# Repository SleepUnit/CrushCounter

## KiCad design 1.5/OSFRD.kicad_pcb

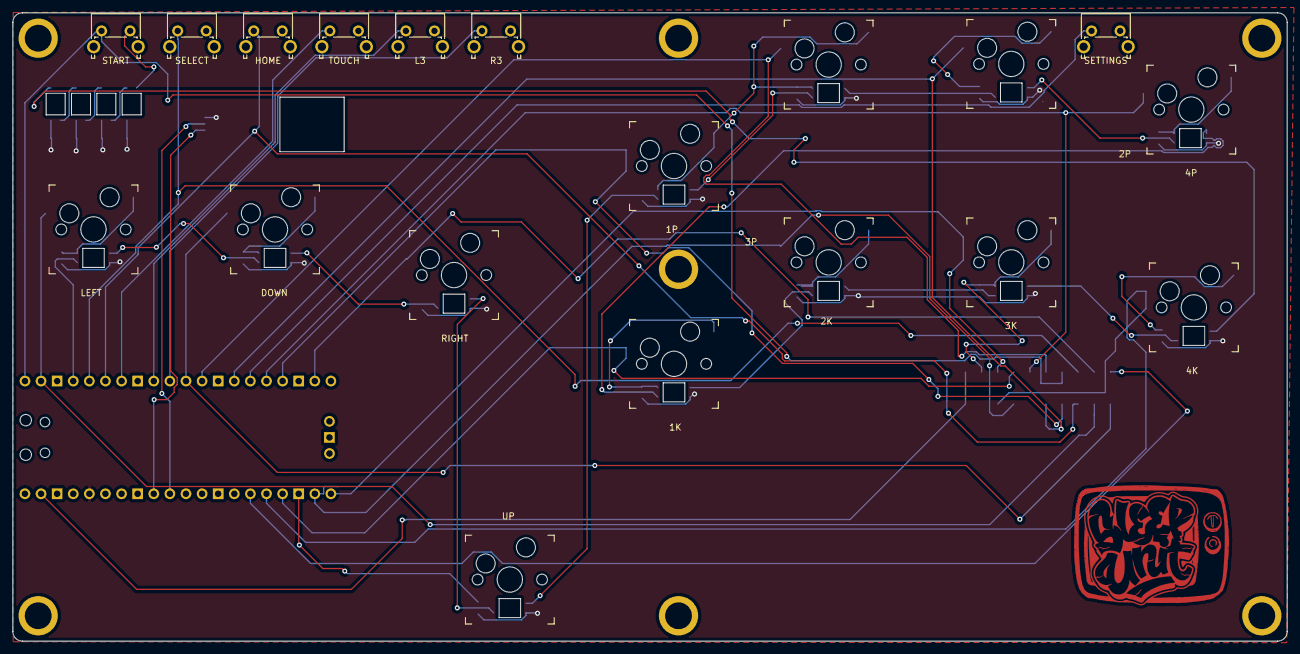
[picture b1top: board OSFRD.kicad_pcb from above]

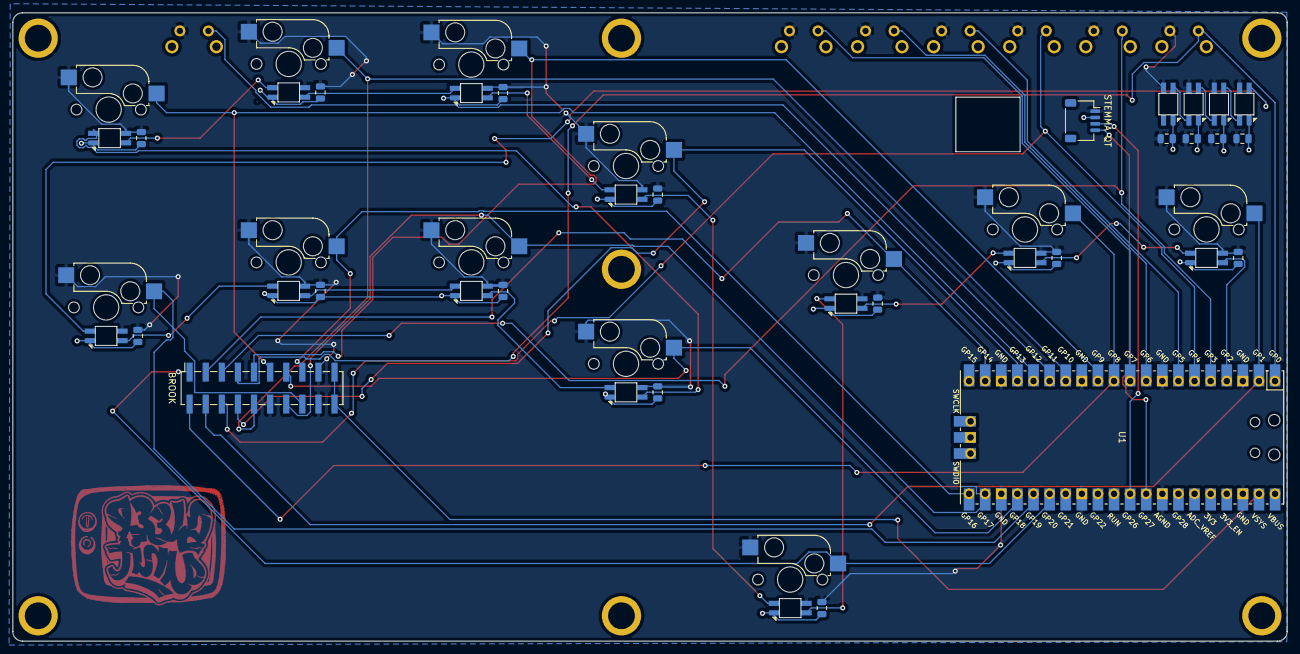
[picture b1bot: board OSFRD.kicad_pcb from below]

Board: 2 copper layers, 201.0 x 99.1 mm, 54 parts (35 on the bottom side), 40 nets.

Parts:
BROOK: 20 Pin; PinSocket_2x10_P2.54mm_Vertical_SMD
HOME: SW_PUSH; SW_Tactile_SPST_Angled_PTS645Vx83-2LFS
L3: SW_PUSH; SW_Tactile_SPST_Angled_PTS645Vx83-2LFS
R3: SW_PUSH; SW_Tactile_SPST_Angled_PTS645Vx83-2LFS
SELECT: SW_PUSH; SW_Tactile_SPST_Angled_PTS645Vx83-2LFS
SETTINGS: SW_PUSH; SW_Tactile_SPST_Angled_PTS645Vx83-2LFS
START: SW_PUSH; SW_Tactile_SPST_Angled_PTS645Vx83-2LFS
STEMMA QT: STEMMA QT; JST_SH_SM04B-SRSS-TB_1x04-1MP_P1.00mm_Horizontal
SW-P1, SW-P2, SW-P3, SW-P4, SW-P5, SW-P6, SW-P7, SW-P8, SW-P9, SW-P10, SW-P11, SW-P12: KEYSW; Kailh_socket_MX
TOUCH: SW_PUSH; SW_Tactile_SPST_Angled_PTS645Vx83-2LFS
U1: Pico; RPi_Pico_SMD_TH
U-CAP1, U-CAP2, U-CAP3, U-CAP4, U-CAP5, U-CAP6, U-CAP7, U-CAP8, U-CAP9, U-CAP10, U-CAP11, U-CAP12, U-CAP13, U-CAP14, U-CAP15, U-CAP16: 0.1uF; C_0805_2012Metric
U-RGB1, U-RGB2, U-RGB3, U-RGB4, U-RGB5, U-RGB6, U-RGB7, U-RGB8, U-RGB9, U-RGB10, U-RGB11, U-RGB12, U-RGB13, U-RGB14, U-RGB15, U-RGB16: Reverse Mounted NeoPixel; SK6812-MINI-E

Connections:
+3V3: STEMMA QT.2, U1.36, U-CAP1.2, U-CAP2.2, U-CAP3.2, U-CAP4.2, U-CAP5.2, U-CAP6.2, U-CAP7.2, U-CAP8.2, U-CAP9.2, U-CAP10.2, U-CAP11.2, U-CAP12.2, U-CAP13.2, U-CAP14.2, U-CAP15.2, U-CAP16.2, U-RGB1.3, U-RGB2.3, U-RGB3.3, U-RGB4.3, U-RGB5.3, U-RGB6.3, U-RGB7.3, U-RGB8.3, U-RGB9.3, U-RGB10.3, U-RGB11.3, U-RGB12.3, U-RGB13.3, U-RGB14.3, U-RGB15.3, U-RGB16.3
+5V: BROOK.19, BROOK.20, U1.39
/Buttons/sheet61498D2A/DataIn: U-RGB5.4, U-RGB6.2
/Buttons/sheet61498D2B/DataIn: U-RGB6.4, U-RGB7.2
/Buttons/sheet61498D2C/DataIn: U-RGB7.4, U-RGB8.2
/Buttons/sheet61498D2D/DataIn: U-RGB8.4, U-RGB9.2
/Buttons/sheet61498D2E/DataIn: U-RGB9.4, U-RGB10.2
/Buttons/sheet61498D2F/DataIn: U-RGB10.4, U-RGB11.2
/Buttons/sheet61498D25/DataIn: U-RGB1.2, U-RGB4.4
/Buttons/sheet61498D26/DataIn: U-RGB2.2, U-RGB3.4
/Buttons/sheet61498D28/DataIn: U-RGB2.4, U-RGB4.2
/Buttons/sheet61498D29/DataIn: U-RGB1.4, U-RGB5.2
/Buttons/sheet61498D30/DataIn: U-RGB11.4, U-RGB12.2
/GPIO0: BROOK.7, START.1, U1.1
/GPIO1: BROOK.4, SW-P3.2, U1.2
/GPIO2: U1.4, U-RGB3.2
/GPIO3: BROOK.5, SELECT.1, U1.5
/GPIO4: BROOK.6, HOME.1, U1.6
/GPIO5: TOUCH.1, U1.7
/GPIO6: L3.1, U1.9
/GPIO7: R3.1, U1.10
/GPIO8: BROOK.2, SW-P2.2, U1.11
/GPIO9: BROOK.9, SW-P6.2, U1.12
/GPIO10: BROOK.10, SW-P7.2, U1.14
/GPIO11: SETTINGS.1, U1.15
/GPIO12: BROOK.11, SW-P8.2, U1.16
/GPIO13: BROOK.8, SW-P5.2, U1.17
/GPIO14: BROOK.3, SW-P4.2, U1.19
/GPIO16: BROOK.15, SW-P11.2, U1.21
/GPIO17: BROOK.14, SW-P10.2, U1.22
/GPIO18: BROOK.13, SW-P9.2, U1.24
/GPIO19: BROOK.16, SW-P12.2, U1.25
/GPIO20: BROOK.1, SW-P1.2, U1.26
/GPIO26_I2C1_SDA: STEMMA QT.3, U1.31
/GPIO27_I2C1_SCL: STEMMA QT.4, U1.32
/PlayerPixels: U-RGB12.4, U-RGB13.2
GND: BROOK.12, BROOK.17, BROOK.18, HOME.2, L3.2, R3.2, SELECT.2, SETTINGS.2, START.2, STEMMA QT.1, SW-P1.1, SW-P2.1, SW-P3.1, SW-P4.1, SW-P5.1, SW-P6.1, SW-P7.1, SW-P8.1, SW-P9.1, SW-P10.1, SW-P11.1, SW-P12.1, TOUCH.2, U1.3, U1.8, U1.13, U1.18, U1.23, U1.28, U1.33, U1.38, U-CAP1.1, U-CAP2.1, U-CAP3.1, U-CAP4.1, U-CAP5.1, U-CAP6.1, U-CAP7.1, U-CAP8.1, U-CAP9.1, U-CAP10.1, U-CAP11.1, U-CAP12.1, U-CAP13.1, U-CAP14.1, U-CAP15.1, U-CAP16.1, U-RGB1.1, U-RGB2.1, U-RGB3.1, U-RGB4.1, U-RGB5.1, U-RGB6.1, U-RGB7.1, U-RGB8.1, U-RGB9.1, U-RGB10.1, U-RGB11.1, U-RGB12.1, U-RGB13.1, U-RGB14.1, U-RGB15.1, U-RGB16.1
unnamed: U-RGB13.4, U-RGB14.2
unnamed: U-RGB14.4, U-RGB15.2
unnamed: U-RGB15.4, U-RGB16.2

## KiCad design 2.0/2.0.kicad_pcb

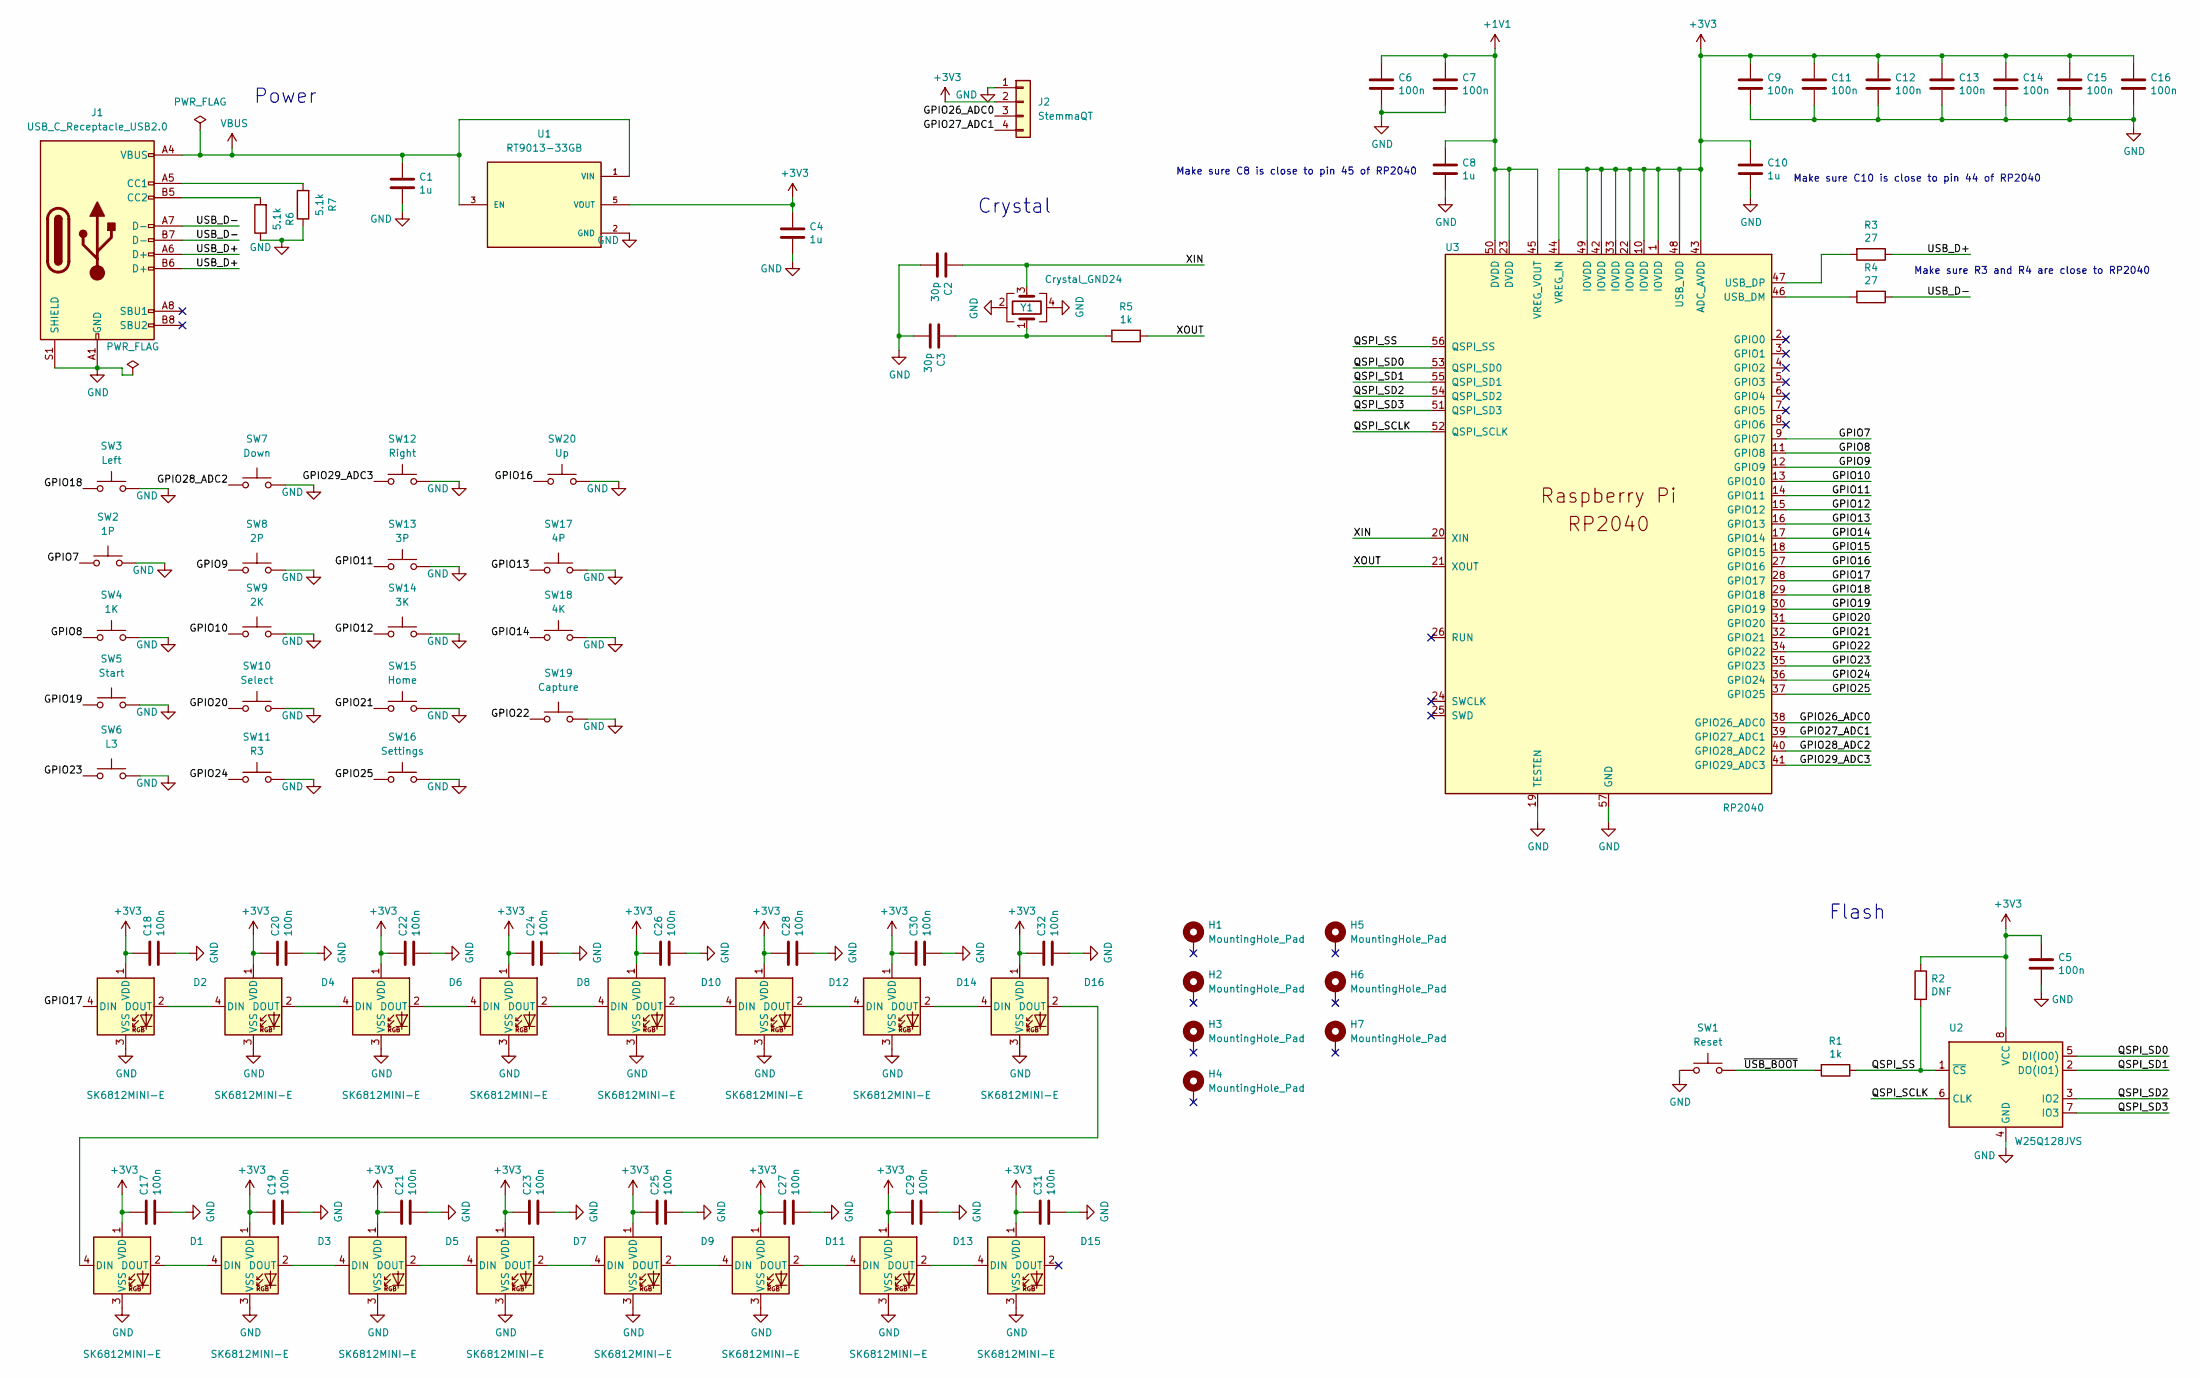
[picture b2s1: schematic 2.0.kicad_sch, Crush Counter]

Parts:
C1, C4, C8, C10: 1u; C_0402_1005Metric; PartNumber CL05A105KA5NQNC; LCSC Part C52923
C2, C3: 30p; C_0402_1005Metric; PartNumber 0402CG300J500NT; LCSC Part C1570
C5, C6, C7, C9, C11, C12, C13, C14, C15, C16, C17, C18, C19, C20, C21, C22, C23, C24, C25, C26, C27, C28, C29, C30, C31, C32: 100n; C_0402_1005Metric; PartNumber CL05B104KO5NNNC; LCSC Part C1525
D1, D2, D3, D4, D5, D6, D7, D8, D9, D10, D11, D12, D13, D14, D15, D16: SK6812MINI-E; MX_SK6812MINI-E; PartNumber SK6812MINI-E; LCSC Part DNF
H1, H2, H3, H4, H5, H6, H7: MountingHole_Pad; Mounting_Wuerth_WA-SMSI-M3_H2mm_9774020360; PartNumber SMTSO3020MTJ; LCSC Part C2915633
J1: USB_C_Receptacle_USB2.0; USB_C_Receptacle_HRO_TYPE-C-31-M-12; PartNumber HRO_TYPE-C-31-M-12; LCSC Part C165948
J2: StemmaQT; JST_SH_SM04B-SRSS-TB_1x04-1MP_P1.00mm_Horizontal; PartNumber SM04B-SRSS-TBLFSN; LCSC Part DNF
R1, R5: 1k; C_0402_1005Metric; PartNumber 0402WGF1001TCE; LCSC Part C11702
R2: DNF; C_0402_1005Metric; PartNumber DNF; LCSC Part DNF
R3, R4: 27; C_0603_1608Metric; PartNumber 0603WAF270JT5E; LCSC Part C25190
R6, R7: 5.1k; C_0402_1005Metric; PartNumber 0402WGF5101TCE; LCSC Part C25905
SW1: Reset; TS-1187A-B-A-B; PartNumber TS-1187A-B-A-B; LCSC Part C318884
SW2: 1P; Kailh_socket_MX; PartNumber PG151101S11; LCSC Part DNF
SW3: Left; Kailh_socket_MX; PartNumber PG151101S11; LCSC Part DNF
SW4: 1K; Kailh_socket_MX; PartNumber PG151101S11; LCSC Part DNF
SW5: Start; EVQP7C01P; PartNumber EVQP7C01P; LCSC Part C388883
SW6: L3; EVQP7C01P; PartNumber EVQP7C01P; LCSC Part C388883
SW7: Down; Kailh_socket_MX; PartNumber PG151101S11; LCSC Part DNF
SW8: 2P; Kailh_socket_MX; PartNumber PG151101S11; LCSC Part DNF
SW9: 2K; Kailh_socket_MX; PartNumber PG151101S11; LCSC Part DNF
SW10: Select; EVQP7C01P; PartNumber EVQP7C01P; LCSC Part C388883
SW11: R3; EVQP7C01P; PartNumber EVQP7C01P; LCSC Part C388883
SW12: Right; Kailh_socket_MX; PartNumber PG151101S11; LCSC Part DNF
SW13: 3P; Kailh_socket_MX; PartNumber PG151101S11; LCSC Part DNF
SW14: 3K; Kailh_socket_MX; PartNumber PG151101S11; LCSC Part DNF
SW15: Home; EVQP7C01P; PartNumber EVQP7C01P; LCSC Part C388883
SW16: Settings; EVQP7C01P; PartNumber EVQP7C01P; LCSC Part C388883
SW17: 4P; Kailh_socket_MX; PartNumber PG151101S11; LCSC Part DNF
SW18: 4K; Kailh_socket_MX; PartNumber PG151101S11; LCSC Part DNF
SW19: Capture; EVQP7C01P; PartNumber EVQP7C01P; LCSC Part C388883
SW20: Up; Kailh_socket_MX; PartNumber PG151101S11; LCSC Part DNF
U1: RT9013-33GB; SOT94P279X129-5N; PARTREV Aprill 2011; LCSC Part C47773
U2: W25Q128JVS; SOIC-8_5.23x5.23mm_P1.27mm; PartNumber W25Q128JVS; LCSC Part C97521
U3: RP2040; RP2040-QFN-56; PartNumber RP2040; LCSC Part C2040
Y1: Crystal_GND24; Crystal_SMD_3225-4Pin_3.2x2.5mm; PartNumber X322512MSB4SI; LCSC Part C9002

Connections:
+1V1: C6.1, C7.1, C8.1, U3.23 (DVDD), U3.45 (VREG_VOUT), U3.50 (DVDD)
+3V3: C4.1, C5.1, C9.1, C10.1, C11.1, C12.1, C13.1, C14.1, C15.1, C16.1, C17.1, C18.1, C19.1, C20.1, C21.1, C22.1, C23.1, C24.1, C25.1, C26.1, C27.1, C28.1, C29.1, C30.1, C31.1, C32.1, D1.1 (VDD), D2.1 (VDD), D3.1 (VDD), D4.1 (VDD), D5.1 (VDD), D6.1 (VDD), D7.1 (VDD), D8.1 (VDD), D9.1 (VDD), D10.1 (VDD), D11.1 (VDD), D12.1 (VDD), D13.1 (VDD), D14.1 (VDD), D15.1 (VDD), D16.1 (VDD), J2.2, R2.1, U1.5 (VOUT), U2.8 (VCC), U3.1 (IOVDD), U3.10 (IOVDD), U3.22 (IOVDD), U3.33 (IOVDD), U3.42 (IOVDD), U3.43 (ADC_AVDD), U3.44 (VREG_IN), U3.48 (USB_VDD), U3.49 (IOVDD)
/GPIO7: SW2.1, U3.9 (GPIO7)
/GPIO8: SW4.1, U3.11 (GPIO8)
/GPIO9: SW8.1, U3.12 (GPIO9)
/GPIO10: SW9.1, U3.13 (GPIO10)
/GPIO11: SW13.1, U3.14 (GPIO11)
/GPIO12: SW14.1, U3.15 (GPIO12)
/GPIO13: SW17.1, U3.16 (GPIO13)
/GPIO14: SW18.1, U3.17 (GPIO14)
/GPIO15: U3.18 (GPIO15)
/GPIO16: SW20.1, U3.27 (GPIO16)
/GPIO17: D2.4 (DIN), U3.28 (GPIO17)
/GPIO18: SW3.1, U3.29 (GPIO18)
/GPIO19: SW5.1, U3.30 (GPIO19)
/GPIO20: SW10.1, U3.31 (GPIO20)
/GPIO21: SW15.1, U3.32 (GPIO21)
/GPIO22: SW19.1, U3.34 (GPIO22)
/GPIO23: SW6.1, U3.35 (GPIO23)
/GPIO24: SW11.1, U3.36 (GPIO24)
/GPIO25: SW16.1, U3.37 (GPIO25)
/GPIO26_ADC0: J2.3, U3.38 (GPIO26_ADC0)
/GPIO27_ADC1: J2.4, U3.39 (GPIO27_ADC1)
/GPIO28_ADC2: SW7.1, U3.40 (GPIO28_ADC2)
/GPIO29_ADC3: SW12.1, U3.41 (GPIO29_ADC3)
/QSPI_SCLK: U2.6 (CLK), U3.52 (QSPI_SCLK)
/QSPI_SD0: U2.5 (DI(IO0)), U3.53 (QSPI_SD0)
/QSPI_SD1: U2.2 (DO(IO1)), U3.55 (QSPI_SD1)
/QSPI_SD2: U2.3 (IO2), U3.54 (QSPI_SD2)
/QSPI_SD3: U2.7 (IO3), U3.51 (QSPI_SD3)
/QSPI_SS: R1.1, R2.2, U2.1 (~CS), U3.56 (QSPI_SS)
/USB_D+: J1.A6 (D+), J1.B6 (D+), R3.1
/USB_D-: J1.A7 (D-), J1.B7 (D-), R4.1
/XIN: C2.1, U3.20 (XIN), Y1.3
/XOUT: R5.1, U3.21 (XOUT)
/~USB_BOOT: R1.2, SW1.2
GND: C1.2, C2.2, C3.2, C4.2, C5.2, C6.2, C7.2, C8.2, C9.2, C10.2, C11.2, C12.2, C13.2, C14.2, C15.2, C16.2, C17.2, C18.2, C19.2, C20.2, C21.2, C22.2, C23.2, C24.2, C25.2, C26.2, C27.2, C28.2, C29.2, C30.2, C31.2, C32.2, D1.3 (VSS), D2.3 (VSS), D3.3 (VSS), D4.3 (VSS), D5.3 (VSS), D6.3 (VSS), D7.3 (VSS), D8.3 (VSS), D9.3 (VSS), D10.3 (VSS), D11.3 (VSS), D12.3 (VSS), D13.3 (VSS), D14.3 (VSS), D15.3 (VSS), D16.3 (VSS), J1.A1 (GND), J1.A12 (GND), J1.B1 (GND), J1.B12 (GND), J1.S1 (SHIELD), J2.1, R6.1, R7.1, SW1.1, SW2.2, SW3.2, SW4.2, SW5.2, SW6.2, SW7.2, SW8.2, SW9.2, SW10.2, SW11.2, SW12.2, SW13.2, SW14.2, SW15.2, SW16.2, SW17.2, SW18.2, SW19.2, SW20.2, U1.2 (GND), U2.4 (GND), U3.19 (TESTEN), U3.57 (GND), Y1.2, Y1.4
unnamed: C3.1, R5.2, Y1.1
unnamed: D1.2 (DOUT), D3.4 (DIN)
unnamed: D1.4 (DIN), D16.2 (DOUT)
unnamed: D2.2 (DOUT), D4.4 (DIN)
unnamed: D3.2 (DOUT), D5.4 (DIN)
unnamed: D4.2 (DOUT), D6.4 (DIN)
unnamed: D5.2 (DOUT), D7.4 (DIN)
unnamed: D6.2 (DOUT), D8.4 (DIN)
unnamed: D7.2 (DOUT), D9.4 (DIN)
unnamed: D10.2 (DOUT), D12.4 (DIN)
unnamed: D8.2 (DOUT), D10.4 (DIN)
unnamed: D11.2 (DOUT), D13.4 (DIN)
unnamed: D9.2 (DOUT), D11.4 (DIN)
unnamed: D12.2 (DOUT), D14.4 (DIN)
unnamed: D13.2 (DOUT), D15.4 (DIN)
unnamed: D14.2 (DOUT), D16.4 (DIN)
unnamed: J1.A5 (CC1), R7.2
unnamed: J1.B5 (CC2), R6.2
unnamed: R3.2, U3.47 (USB_DP)
unnamed: R4.2, U3.46 (USB_DM)
VBUS: C1.1, J1.A4 (VBUS), J1.A9 (VBUS), J1.B4 (VBUS), J1.B9 (VBUS), U1.1 (VIN), U1.3 (EN)

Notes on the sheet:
Make sure C10 is close to pin 44 of RP2040
Power
Flash
Make sure R3 and R4 are close to RP2040
Make sure C8 is close to pin 45 of RP2040
Crystal

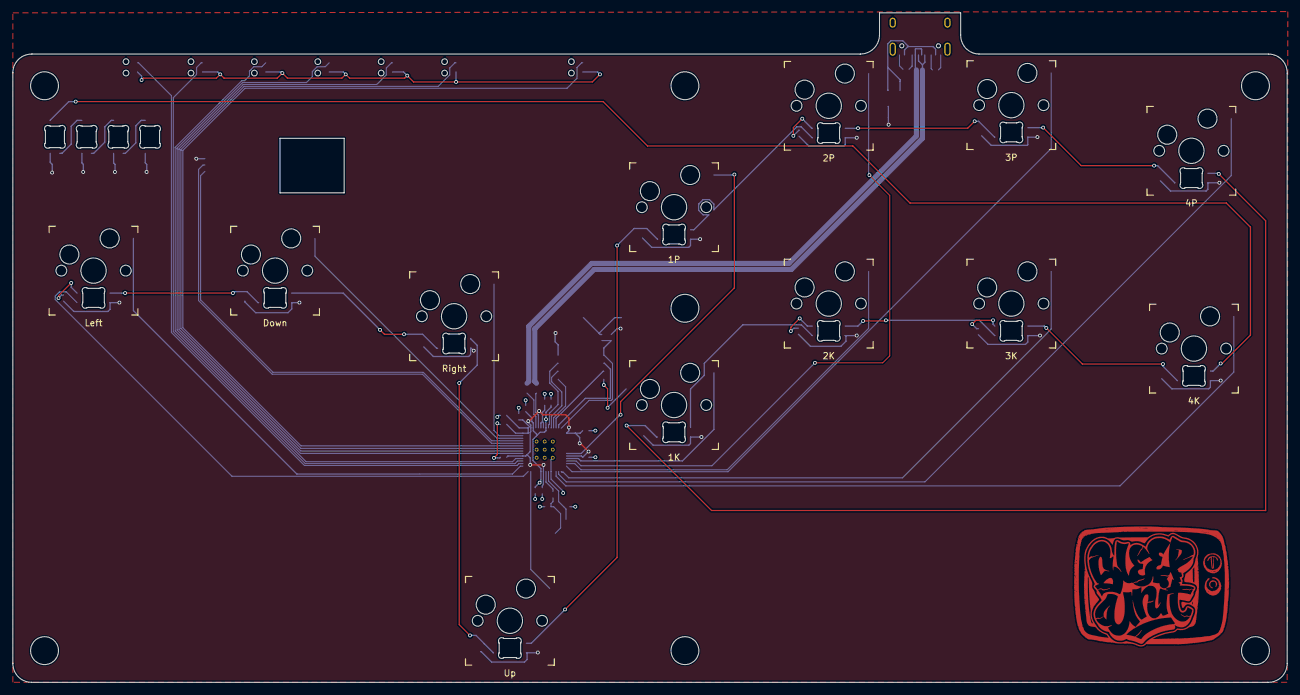
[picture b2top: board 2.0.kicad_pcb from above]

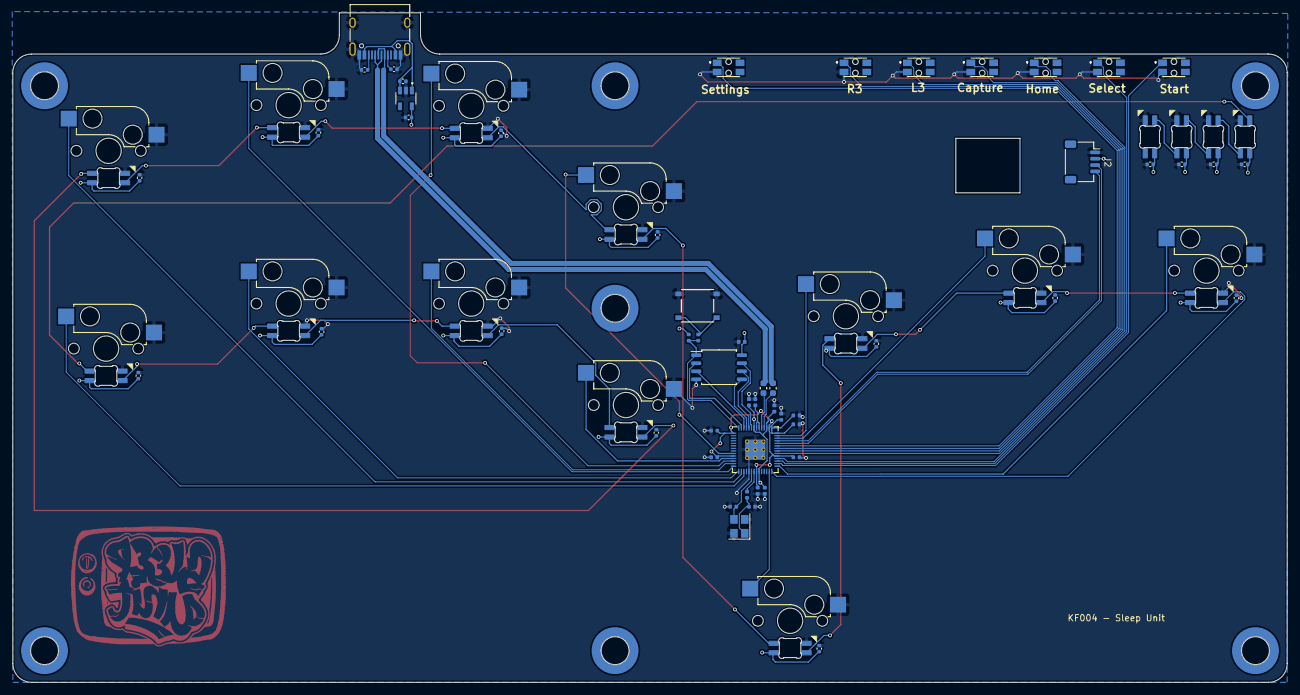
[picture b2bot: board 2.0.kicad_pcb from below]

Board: 2 copper layers, 201.0 x 105.6 mm, 88 parts (76 on the bottom side), 57 nets.

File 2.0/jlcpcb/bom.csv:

Comment,Designator,Footprint,LCSC
1u,"C1,C4,C8,C10",Capacitor_SMD:C_0402_1005Metric,C52923
30p,"C2,C3",Capacitor_SMD:C_0402_1005Metric,C1570
100n,"C5,C6,C7,C9,C11,C12,C13,C14,C15,C16,C17,C18,C19,C20,C21,C22,C23,C24,C25,C26,C27,C28,C29,C30,C31,C32",Capacitor_SMD:C_0402_1005Metric,C1525
SK6812MINI-E,"D1,D2,D3,D4,D5,D6,D7,D8,D9,D10,D11,D12,D13,D14,D15,D16",kicad-keyboard-parts:MX_SK6812MINI-E,DNF
MountingHole_Pad,"H1,H2,H3,H4,H5,H6,H7",Mounting_Wuerth:Mounting_Wuerth_WA-SMSI-M3_H2mm_9774020360,C2915633
USB_C_Receptacle_USB2.0,J1,Connector_USB:USB_C_Receptacle_HRO_TYPE-C-31-M-12,C165948
1k,"R1,R5",Capacitor_SMD:C_0402_1005Metric,C11702
DNF,R2,Capacitor_SMD:C_0402_1005Metric,DNF
27,"R3,R4",Capacitor_SMD:C_0603_1608Metric,C25190
5.1k,"R6,R7",Capacitor_SMD:C_0402_1005Metric,C25905
Reset,SW1,2.0:TS-1187A-B-A-B,C318884
1P,SW2,2.0:Kailh_socket_MX,DNF
Left,SW3,2.0:Kailh_socket_MX,DNF
1K,SW4,2.0:Kailh_socket_MX,DNF
Start,SW5,SamacSys_Parts:EVQP7C01P,C388883
L3,SW6,SamacSys_Parts:EVQP7C01P,C388883
Down,SW7,2.0:Kailh_socket_MX,DNF
2P,SW8,2.0:Kailh_socket_MX,DNF
2K,SW9,2.0:Kailh_socket_MX,DNF
Select,SW10,SamacSys_Parts:EVQP7C01P,C388883
R3,SW11,SamacSys_Parts:EVQP7C01P,C388883
Right,SW12,2.0:Kailh_socket_MX,DNF
3P,SW13,2.0:Kailh_socket_MX,DNF
3K,SW14,2.0:Kailh_socket_MX,DNF
Home,SW15,SamacSys_Parts:EVQP7C01P,C388883
Settings,SW16,SamacSys_Parts:EVQP7C01P,C388883
4P,SW17,2.0:Kailh_socket_MX,DNF
4K,SW18,2.0:Kailh_socket_MX,DNF
Capture,SW19,SamacSys_Parts:EVQP7C01P,C388883
Up,SW20,2.0:Kailh_socket_MX,DNF
RT9013-33GB,U1,2.0:SOT94P279X129-5N,C47773
W25Q128JVS,U2,Package_SO:SOIC-8_5.23x5.23mm_P1.27mm,C97521
RP2040,U3,RP2040_minimal:RP2040-QFN-56,C2040
Crystal_GND24,Y1,Crystal:Crystal_SMD_3225-4Pin_3.2x2.5mm,C9002

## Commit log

2021-09-02 Initial Public Release of In Progress OSFRDv2
2021-09-15 v1.5 Finalized
2021-10-29 Docs for the v1.5
2021-10-29 Documentation spelling/grammar i ssues
2022-05-07 Added 2.0 finally
